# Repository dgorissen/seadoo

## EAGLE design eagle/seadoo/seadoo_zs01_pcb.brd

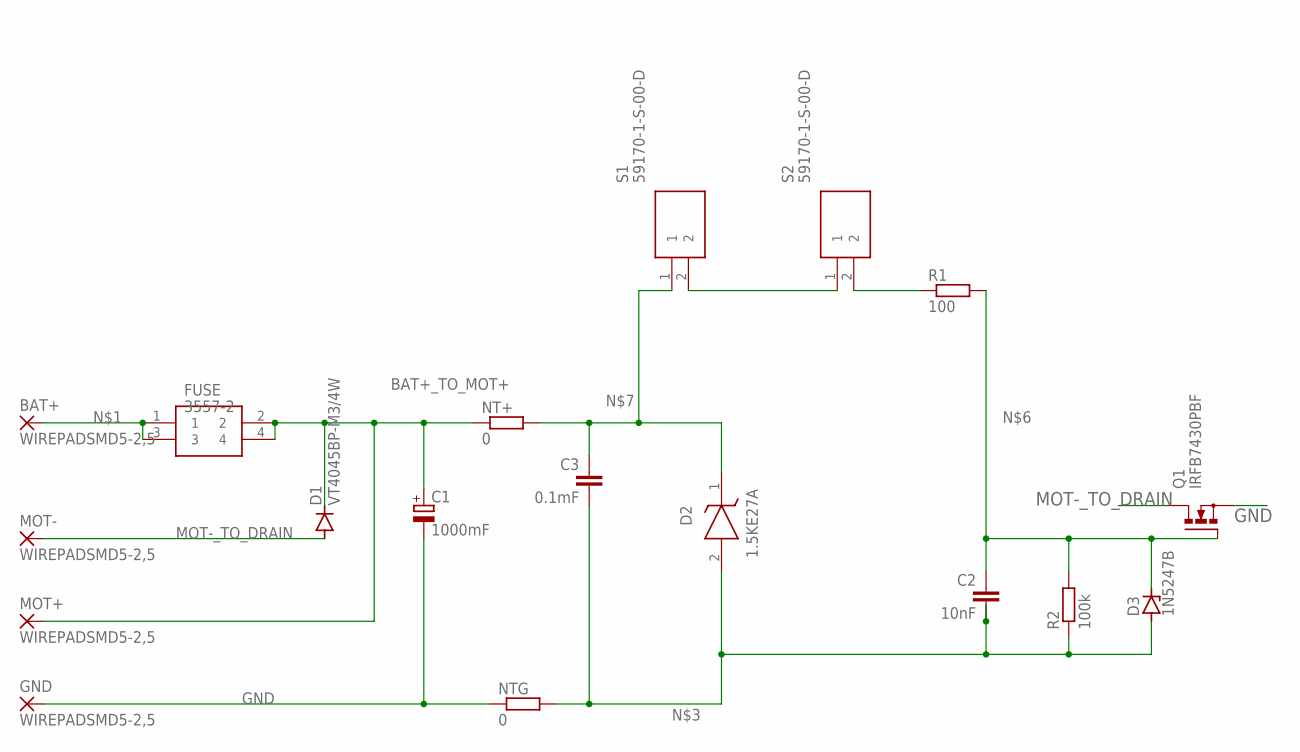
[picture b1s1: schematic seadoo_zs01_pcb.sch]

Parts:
BAT+: WIREPADSMD5-2,5; 5-2,5
C1: 1000mF; TT5D11
C2: 10nF; C5B3
C3: 0.1mF; C5B3
D1: VT4045BP-M3/4W; TO220AC
D2: 1.5KE27A; DIOAD2920W106L900D505
D3: 1N5247B; P1Z12
FUSE: 3557-2
GND: WIREPADSMD5-2,5; 5-2,5
MOT+: WIREPADSMD5-2,5; 5-2,5
MOT-: WIREPADSMD5-2,5; 5-2,5
NT+: 0; R1218
NTG: 0; R1218
Q1: IRFB7430PBF; TO220BH
R1: 100; 0204/7
R2: 100k; 0204/7
S1, S2: 59170-1-S-00-D; 591701S00D

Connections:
BAT+_TO_MOT+: C1.+, D1.C, FUSE.2, FUSE.4, MOT+.1, NT+.1
GND: C1.-, GND.1, NTG.1, Q1.S
MOT-_TO_DRAIN: D1.A, MOT-.1, Q1.D
unnamed: BAT+.1, FUSE.1, FUSE.3
unnamed: C2.2, C3.2, D2.2 (A), D3.A, NTG.2, R2.1
unnamed: S1.2, S2.1
unnamed: R1.1, S2.2
unnamed: C2.1, D3.C, Q1.G, R1.2, R2.2
unnamed: C3.1, D2.1 (K), NT+.2, S1.1

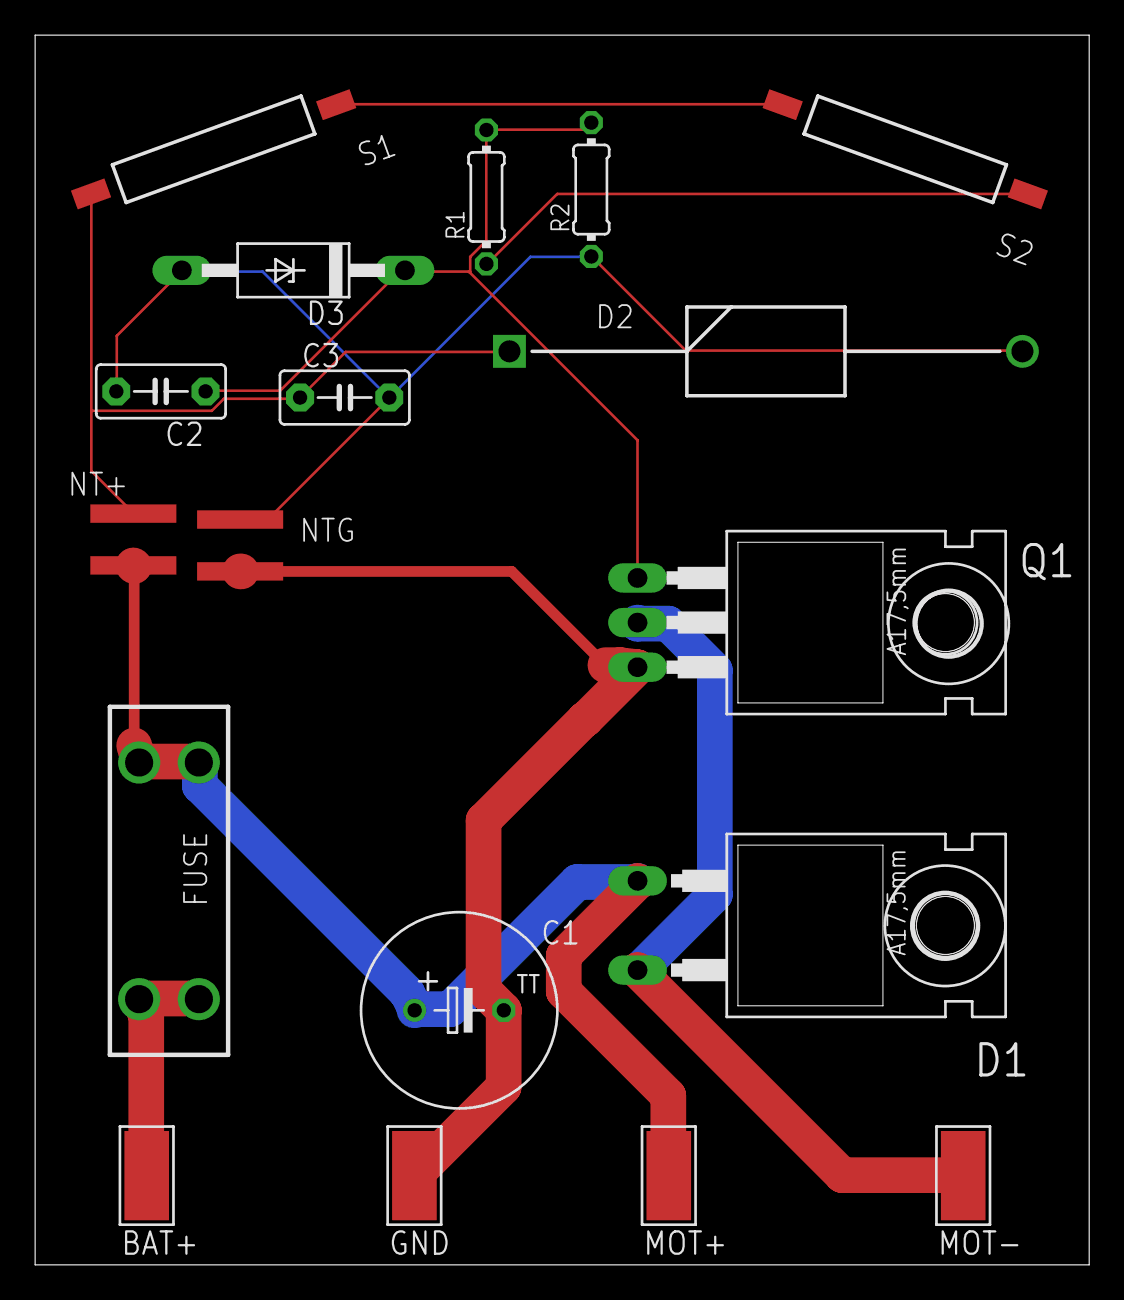
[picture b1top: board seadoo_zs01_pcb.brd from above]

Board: 2 copper layers, 60.0 x 70.0 mm, 20 parts (0 on the bottom side), 9 nets.

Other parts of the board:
U$1, U$2: 3,6

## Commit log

2026-02-05 As sent off for first fabrication
